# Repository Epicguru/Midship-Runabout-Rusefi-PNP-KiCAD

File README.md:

### Original Repo:
https://github.com/threepotMR2/Midship-Runabout-Rusefi-PNP-pcb

## MRR Epicguru Fork
This is a WIP KiCAD version of @threepotMR2 's Midship Runabout Rusefi project, which aims to be an affordable Plug & Play programmable ECU for the 1ZZFE or 2ZZ MR2 Spyder.  

**[Download the latest production files here (Gerbers, BOM, CPL)](https://github.com/Epicguru/Midship-Runabout-Rusefi-PNP-KiCAD/releases/latest)**  
I do not recommend ordering this version of the board yet, it is untested.

Compared to the original, this has been done in [KiCAD 10](https://www.kicad.org/), which is free open source schematic and PCB design software. If you also use the [JLCPCB Tools plugin](https://github.com/bouni/kicad-jlcpcb-tools) then you will get all parts ready to send for manufacturing with JLCPCB in one click (though pay attention to the rotation of components! I have not yet done the rotation corrections in the project, so you will need to do it when you upload the production files!).  

<p align="center">

  <br>

</p>

## Changes compared to original

### Important
- It is now a 4-layer board with signal on the front and back and two inner ground layers. This should improve signal integrity and reduce noise, especially under the VR circuits and the new 3.3v buck converter. This only adds around 1.5 EUR per board.
- Added TVS protection diodes  to the high and low-side relay switches. I haven't been able to verify whether the car's relays have built-in diodes (if they do they don't show up on wiring diagrams), but if they don't then each time they are switched then the coils will shove huge voltage spikes through the PhotoMOS which will kill them over time. If they do have built-in diodes, adding these extra ones doesn't hurt.
- Changed PhotoMOS fuses: the original fuses were 1A fast-blow fuses. The PhotoMOS are rated for 0.55A continuous. I have replaced the fuses with 0.5A hold, 1A trip resettable PTCs. It means that they still protect against short-circuits, but don't need replacing in that event.
- Replaced various resistors that were out-of-spec:
  - **R24**: This resistor was a 330 Ohm 0603 part that was limiting current to the PhotoMOS. The resistance was fine, allowing around 40mA through the LED vs 50mA max spec, but at that current it was dissipating around 0.5W of heat which is well above the 0.1W it is rated for. The resistor would cook over time, especially in a sealed case. It failing would turn the main relay off which could range from very annoying to really dangerous.
  - **R22**: This is the BEAN pull-up resistor. Resistance is fine but again it burns too much power: 0.2W in a 0.1W spec part. Changed to a larger package rated for 0.5W, same resistance.
  - **R15**: Tach output resistor. Did not really need changing but it was swapped for a higher power anti-surge resistor that just means that if you accidentally short the tach output (such as touching tach to chassis when removing dash) it won't burn the resistor out.
- Changed 12V input surge clamp to 18V, 600W part to protect U10 (buck converter) and U14 (tach output opto). The original 15V standoff was a little too close to normal charging voltage for my liking, increasing to 18 won't hurt anything on the circuit. I still need to improve this protection, but it should be fine for now.

### Other fixes & changes
- Fixed A/C pressure switch hardware: the manual says that you will get between 9V and 14V when pressure is good, and '-' when the pressure is bad. I haven't been able to figure out if that means LOW or just floating, but it's a problem either way.   
The problem with the original circuitry is that it relied on the voltage difference between the switch and VIN. If VIN happens to be too close to the P/S voltage, then the LED will not turn on. That leaves GPIO21 floating. Because there is no pull-up/down enabled in the firmware, I suspect that it was simply drifting HIGH which is why it was still working.  
More concerning is that if there is a fault: if the switch goes LOW then all of VIN is going to go through the LED, which puts R13 out-of-spec (~0.2W rated at 0.1W), and it will also still read as 'OK' on the ESP32. If the switch goes floating then we are back to the floating GPIO21 scenario, where it will probably still drift high.
  - I've fixed this by shuffling things around so that the A/C switch is now the LED driver. If it goes LOW or floating, then the LED turns off. If the LED turns off then there is an additional pull-down resistor on the output to make sure that it is low without having to rely on firmware pull-down.  
    
- Swapped 3.3v LDO for an automotive-grade buck converter. The LDO is fine for tiny currents but as current increases it starts to burn lots of power.
  - On the original board it was around 1.4W of heat produced, including the optocouplers. If you want to connect to the ESP32 Wifi then it could increase up to around 1.7W, which will get very toasty in an enclosed case. On the original board there is also a mistake that makes this worse, the large tab is not connected to the ground plane. The large tab is supposed to act as a heat sink by putting heat into the copper. It is not connected and so it will get even hotter. The LM2937 has a thermal-shutdown of 150C which isn't hard to reach without a heatsink and that much current. It's probably fine with the ESP32 WiFi turned off and a heat sink on it.  

  - The buck converter is a lot more efficient and costs almost exactly the same. The only disadvantage is that it can't handle huge input voltage spikes, see notes above.
- Populated all spare connections on the 'magic 5th connector'. There are now:
  - 4 analogue inputs (one has a 500k pull-down).
  - 1 digital input with a 10k pull-up.
- Added 1-pin male headers to the missing slots on the board.
- All male headers are now gold-plated and rated for 3A each. This should allow using female headers soldered on to the uaEFI to allow you to swap between daughter-boards without desoldering the RUS. Needs testing, might be too tall for the stock ECU case.
- Almost all power traces have been beefed up, especially the 12V input. 12V in can carry up to 4A if you are using the onboard wideband controller, so I've erred on the side of caution.
- Improved clearance around the crank and cam VR traces and do not route them through vias: these are very high voltage and noisy, so they have been kept on the top layer and away from other inputs as much as possible.

### Minor changes
- Added a jumper for the CAN bus termination resistor. If you have an external dash or logging device that has one soldered in, you can just remove the jumper rather than having to de-solder it.
- Added a mirrored set of female headers for the ESP32. That just makes probing easier, and lets you quite easily bodge in new circuitry. It may make it so that you have to use a 90-degree USB connector on the RUS since there is less space now.
- Added missing second ESP32 GND connection
- Added several test-points.

## Doubts
- The original board the stock OX1A pin was tied to signal ground. I'm not sure if that is a mistake or if Threepot was using the stock sensor plug for something else. I've added a jumper to either keep it tied to signal ground or just leave it floating. If the user wants to keep the stock sensor plugged in, for some reason, then the jumper should not be used.
- The original schematic and gerber/BOM files are slightly out-of-sync and the most significant change seems to be the VR conditioning capacitors. I haven't spent enough time researching these VR chips to know what the correct values are, so I've trusted what the JLCPCB BOM part number says and used those capacitor values.

## Does it work?
No clue, I've ordered one to try.  
I'll update the repo once I have had a chance to test it.

## Can it run the stock car?
No, you need an external wideband sensor in the exhaust, and the stock narrowband sensors need to be removed or they will be destroyed.

## How much does it cost?
You have to source the connector which can be had for around 25$ straight from the supplier, or 45$ from the RusEFI ebay shop.  
You also need the 17 pin 5th connector which is just a few dollars from China.
The board itself, with the components specified, costs around 70-100$ from JLCPCB. If you order many of them, the cost will be closer to 60$ per assembled board. If you order just two (minimum amount), expect around 100$ per board.  
The RusEFI uaEFI is around 150$.  

Overall, including the rusEFI & connectors, shipping, import duties and taxes, it cost me around 250 EUR per ECU when building two of them.

## Future plans/work
- [ ] Improve power input protections, including constant reverse polarity protection.
- [ ] Add ESD protection to 5th connector pins.
- [ ] Add ADC chip(s) and screw terminals. Using LUA scripting, you can effectively get 2 more 'free' analogue inputs to the ECU which can be used for anything, and you can get up to 6 additional analogue inputs that can be used for just logging.  
But, you can also use any number of inputs to be applied directly to the tune, or used to replace un-populated physical pins. That can be used to do two interesting things:
   - Create custom buttons/switches that do things like toggle launch control, boost control etc. without having to use any of the ECU's limited physical/virtual inputs.
   - Effectively allows you to 're-wire' unused physical pins without having to actually solder anything on the RUS.

## Are these available/for sale?
Keeping with the spirit of @threepotMR2 's MRR project, this version is open source. You can download all the files needed to have this manufactured, and you can buy a rusEFI uaEFI. If you know how to solder and have ~300$ to burn, you can get everything you need.  

I would like to eventually sell a complete assembled kit, including a 3D printed case, MAP air input, USB port etc. completely ready for use without having to touch the original ECU. I also have a gauge pod project, intended for MR2 turbo cars, that works with this ECU, which I would like to publish and maybe sell.  

ThreepotMR2 plans on selling his design as a kit, so that will be the place to buy one especially if you live in the UK. Since this is 99% his design, work and months testing I will not be selling these directly in the foreseeable future.  

In the future, if he isn't bothered by it, I might still turn these into a product that I sell directly which I'm sure people in Europe would appreciate: shipping and import duty costs are half of the price for most of these components and boards, so extra inter-continental fees really hurt.

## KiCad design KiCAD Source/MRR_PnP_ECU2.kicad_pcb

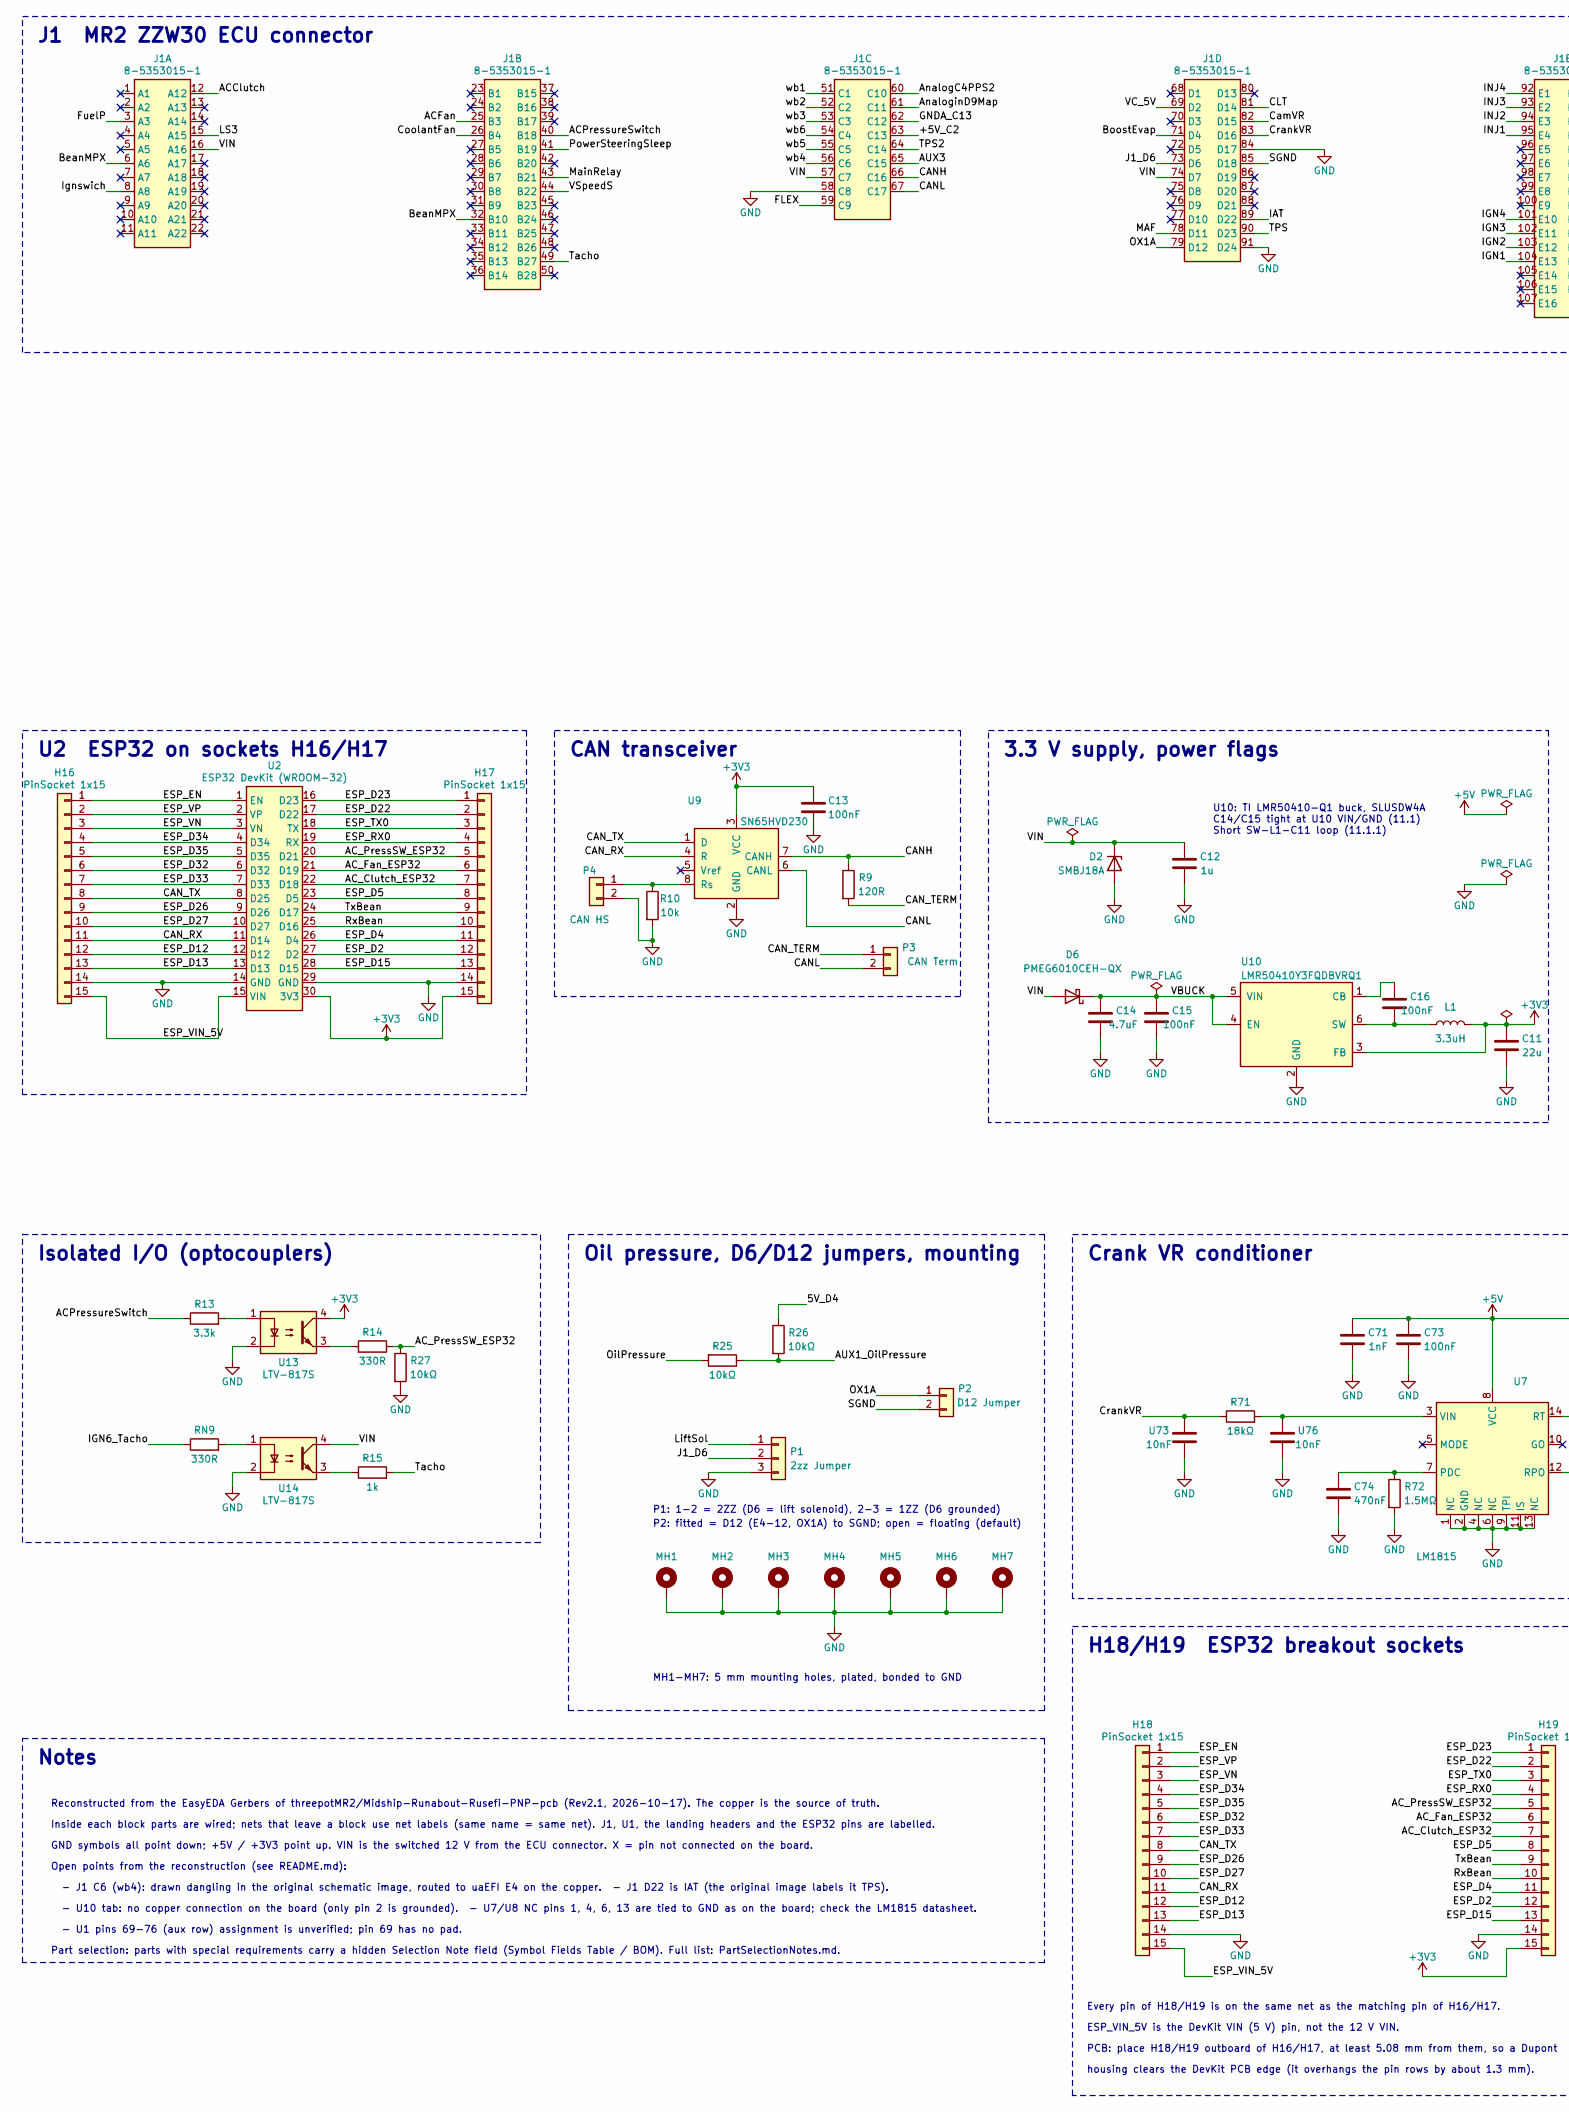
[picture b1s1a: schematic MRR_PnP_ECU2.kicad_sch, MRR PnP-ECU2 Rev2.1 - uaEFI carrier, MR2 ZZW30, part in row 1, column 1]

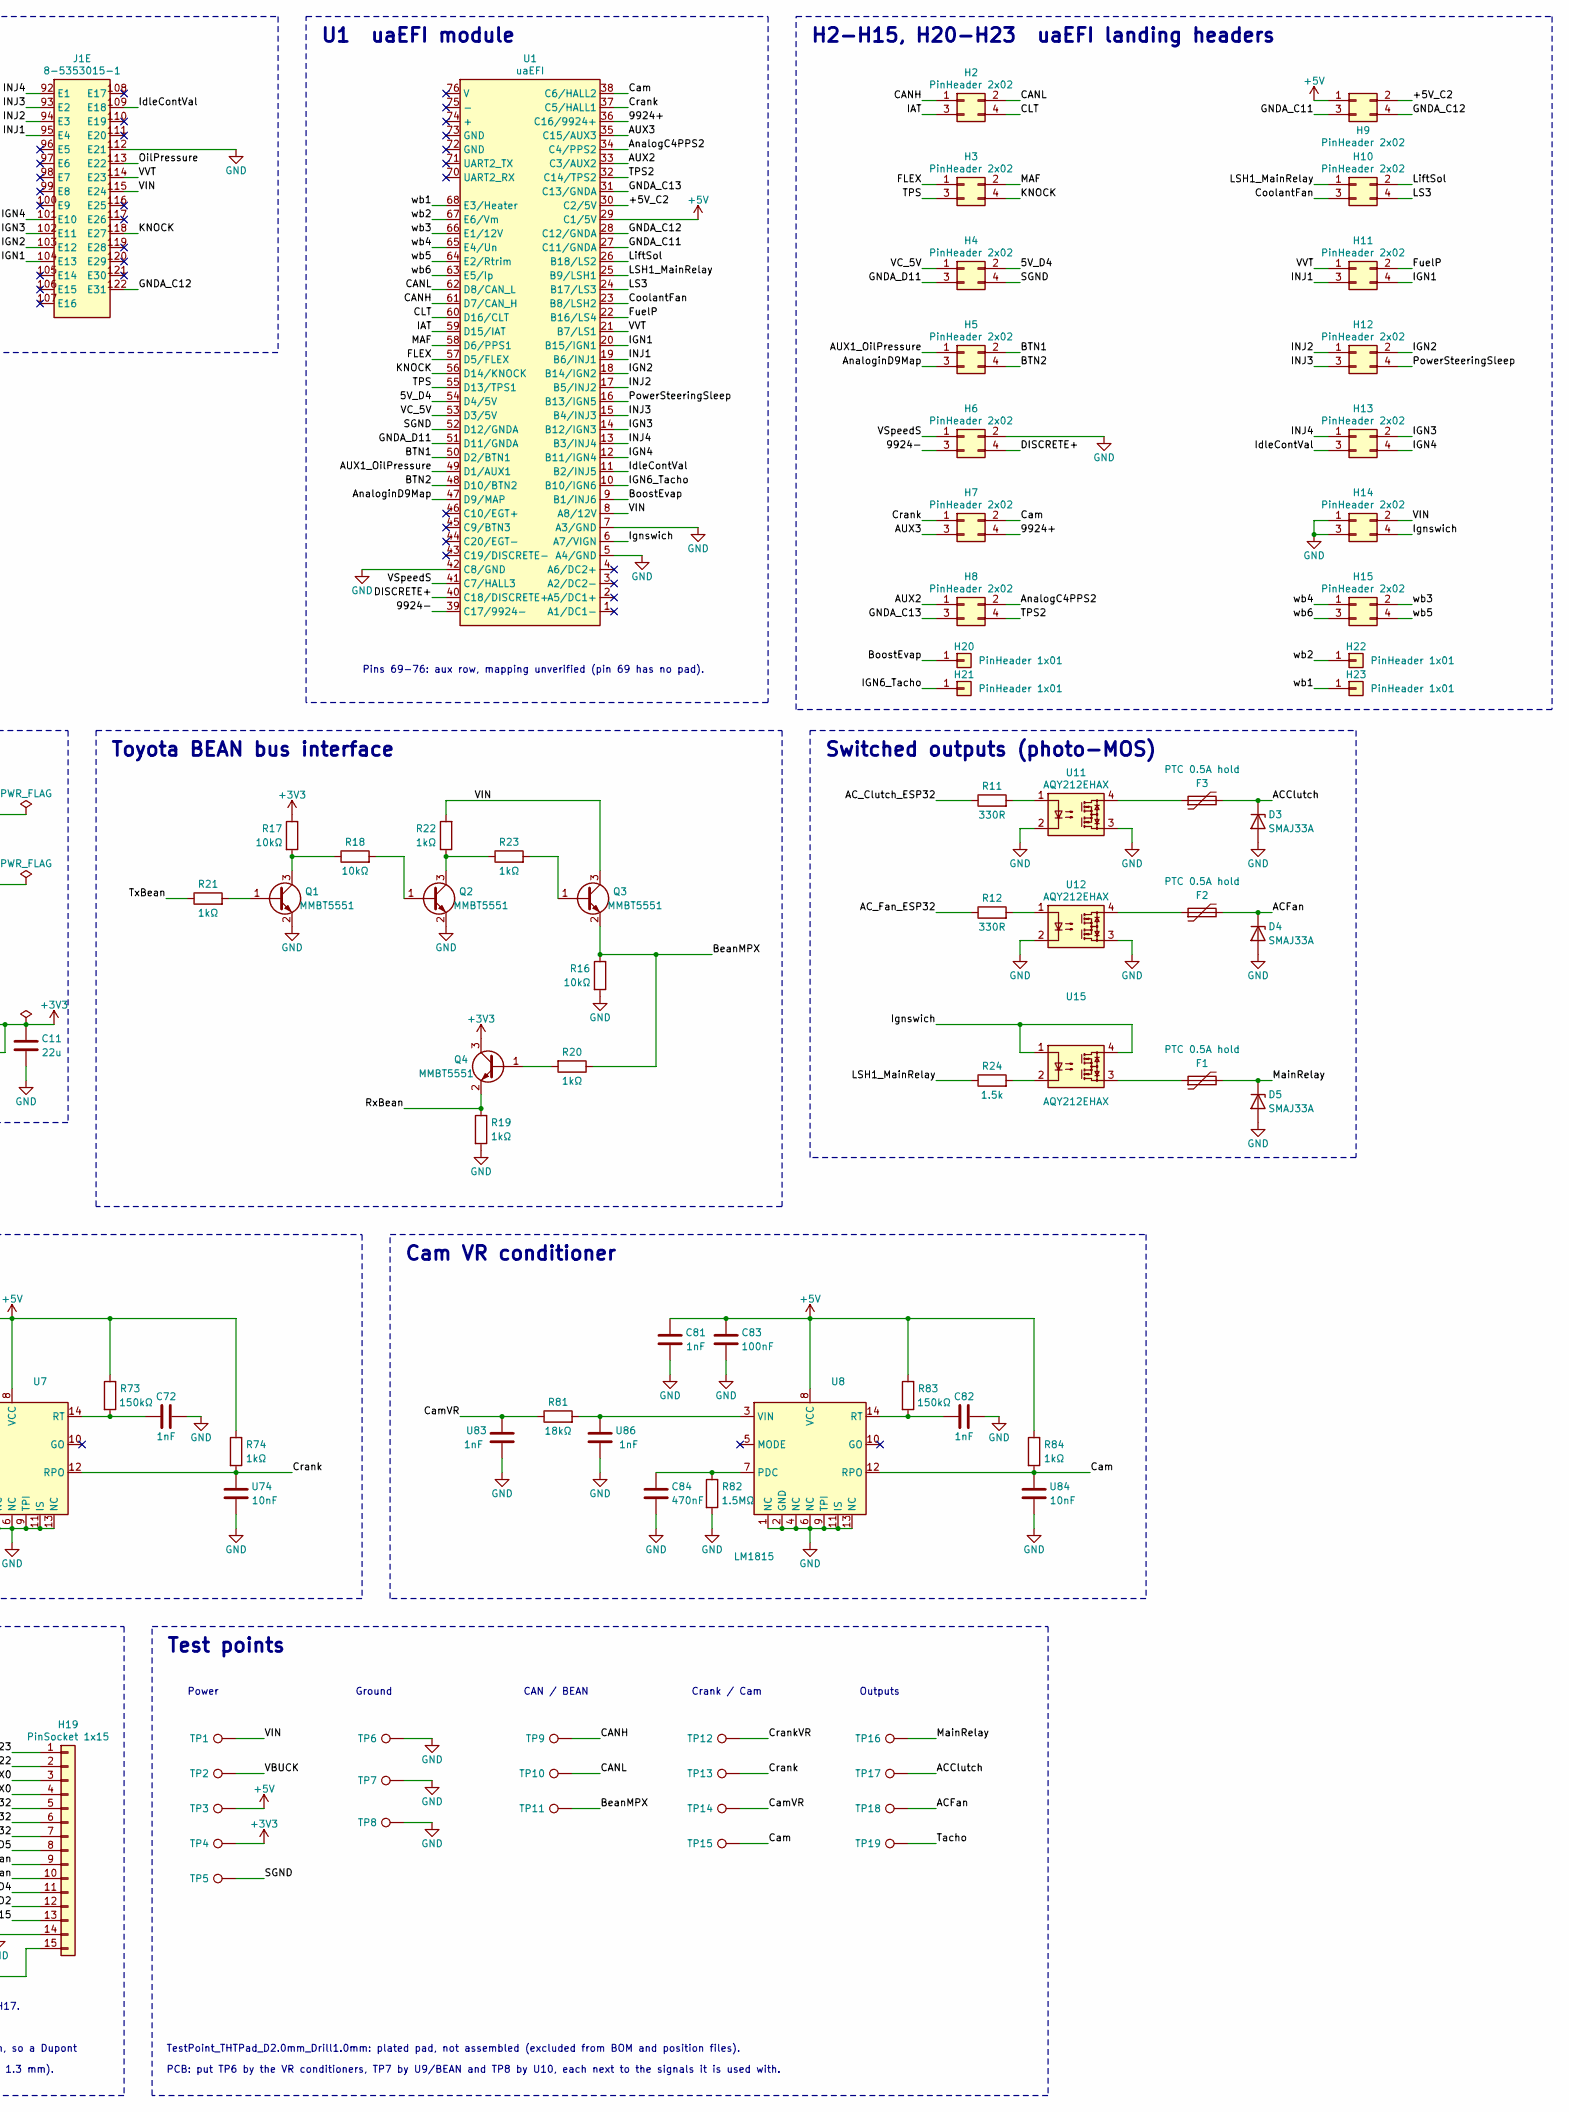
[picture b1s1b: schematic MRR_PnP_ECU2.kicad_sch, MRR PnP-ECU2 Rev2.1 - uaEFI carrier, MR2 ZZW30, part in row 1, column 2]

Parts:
C11: 22u; C_1206_3216Metric; MPN CL31A226KAHNNNE; LCSC C12891
C12: 1u; C_0603_1608Metric; MPN CL10B105KB8NQNC; LCSC C5199872
C13, C15, C16, C73, C83: 100nF; C_0603_1608Metric; MPN CC0603KRX7R9BB104; LCSC C14663
C14: 4.7uF; C_0805_2012Metric; MPN GRM21BZ71H475KE15L; LCSC C437557
C71, C81: 1nF; C_0603_1608Metric; MPN CL10B102KB8NNNC; LCSC C1588
C72, C82: 1nF; C_0603_1608Metric; MPN GCM1885C2A102JA16D; LCSC C437457
C74, C84: 470nF; C_0603_1608Metric; MPN CL10B474KA8NNNC; LCSC C1623
D2: SMBJ18A; D_SMB; MPN SMBJ18AQ; LCSC C5861908
D3, D4, D5: SMAJ33A; D_SMA; MPN SMAJ33A; LCSC C41376399
D6: PMEG6010CEH-QX; D_SOD-123F; MPN PMEG6010CEH-QX; LCSC C5311567
F1, F2, F3: PTC 0.5A hold; Fuse_1206_3216Metric; MPN JK-nSMD050-30; LCSC C720075
H2, H3, H4, H5, H6, H7, H8, H9, H10, H11, H12, H13, H14, H15: PinHeader 2x02; PinHeader_2x02_P2.54mm_uaEFI; MPN 2.54-2*2PPin; LCSC C66690
H16, H17, H18, H19: PinSocket 1x15; PinSocket_1x15_P2.54mm_Vertical; MPN B-2200S15P-A120; LCSC C124408
H20, H21, H22, H23: PinHeader 1x01; PinHeader_1x01_P2.54mm_uaEFI; MPN 2.54-1*1PPin; LCSC C81276
J1: 8-5353015-1; Toyota_ZZW30_ECU_122pin_MRR
L1: 3.3uH; L_Sunlord_SWPA4030S; MPN SWPA4030S3R3MT; LCSC C15269
MH1, MH2, MH3, MH4, MH5, MH6, MH7: MountingHole 5mm; MountingHole_5mm_Pad_7mm
P1: 2zz Jumper; PinHeader_1x03_P2.54mm_Vertical; MPN PZ254V-11-03P; LCSC C2937625
P2: D12 Jumper; PinHeader_1x02_P2.54mm_Vertical; MPN PZ254V-11-02P; LCSC C492401
P3: CAN Term; PinHeader_1x02_P2.54mm_Vertical; MPN PZ254V-11-02P; LCSC C492401
P4: CAN HS; PinHeader_1x02_P2.54mm_Vertical; MPN PZ254V-11-02P; LCSC C492401
Q1, Q2, Q3, Q4: MMBT5551; SOT-23; MPN MMBT5551(RANGE:200-300); LCSC C2145
R9: 120R; R_0603_1608Metric; MPN 0603WAF1200T5E; LCSC C22787
R10: 10k; R_0603_1608Metric; MPN 0603WAF1002T5E; LCSC C25804
R11, R12, R14: 330R; R_0603_1608Metric; MPN 0603WAF3300T5E; LCSC C23138
R13: 3.3k; R_0603_1608Metric; MPN 0603WAF3301T5E; LCSC C22978
R15: 1k; R_0603_1608Metric; MPN ESR03EZPF1001; LCSC C2653986
R16, R17, R18, R25, R26, R27: 10kΩ; R_0603_1608Metric; MPN 0603WAF1002T5E; LCSC C25804
R19, R20, R21, R23, R74, R84: 1kΩ; R_0603_1608Metric; MPN 0603WAF1001T5E; LCSC C21190
R22: 1kΩ; R_1210_3225Metric; MPN 1210W2F1001T5E; LCSC C52444
R24: 1.5k; R_1206_3216Metric; MPN 1206W4F1501T5E; LCSC C26030
R71, R81: 18kΩ; R_1210_3225Metric; MPN 1210W2F1802T5E; LCSC C67557
R72, R82: 1.5MΩ; R_0603_1608Metric; MPN 0603WAF1504T5E; LCSC C4172
R73, R83: 150kΩ; R_0603_1608Metric; MPN 0603WAF1503T5E; LCSC C22807
RN9: 330R; R_0603_1608Metric; MPN 0603WAF3300T5E; LCSC C23138
TP1: VIN; TestPoint_THTPad_D2.0mm_Drill1.0mm
TP2: VBUCK; TestPoint_THTPad_D2.0mm_Drill1.0mm
TP3: +5V; TestPoint_THTPad_D2.0mm_Drill1.0mm
TP4: +3V3; TestPoint_THTPad_D2.0mm_Drill1.0mm
TP5: SGND; TestPoint_THTPad_D2.0mm_Drill1.0mm
TP6, TP7, TP8: GND; TestPoint_THTPad_D2.0mm_Drill1.0mm
TP9: CANH; TestPoint_THTPad_D2.0mm_Drill1.0mm
TP10: CANL; TestPoint_THTPad_D2.0mm_Drill1.0mm
TP11: BeanMPX; TestPoint_THTPad_D2.0mm_Drill1.0mm
TP12: CrankVR; TestPoint_THTPad_D2.0mm_Drill1.0mm
TP13: Crank; TestPoint_THTPad_D2.0mm_Drill1.0mm
TP14: CamVR; TestPoint_THTPad_D2.0mm_Drill1.0mm
TP15: Cam; TestPoint_THTPad_D2.0mm_Drill1.0mm
TP16: MainRelay; TestPoint_THTPad_D2.0mm_Drill1.0mm
TP17: ACClutch; TestPoint_THTPad_D2.0mm_Drill1.0mm
TP18: ACFan; TestPoint_THTPad_D2.0mm_Drill1.0mm
TP19: Tacho; TestPoint_THTPad_D2.0mm_Drill1.0mm
U1: uaEFI; uaEFI_Carrier_MRR
U2: ESP32 DevKit (WROOM-32); ESP32_DevKit_30pin_MRR; MPN ESP32 WROOM-32 ESP32-S
U7, U8: LM1815; SOIC-14_3.9x8.7mm_P1.27mm; MPN LM1815MX/NOPB; LCSC C2878578
U9: SN65HVD230; SOIC-8_3.9x4.9mm_P1.27mm; MPN SN65HVD230DR; LCSC C12084
U10: LMR50410Y3FQDBVRQ1; SOT-23-6; MPN LMR50410Y3FQDBVRQ1; LCSC C5219374
U11, U12, U15: AQY212EHAX; SMDIP-4_W9.53mm; MPN AQY212EHAX; LCSC C29276
U13, U14: LTV-817S; SMDIP-4_W9.53mm; MPN LTV-817S-TA1-C; LCSC C109227
U73: 10nF; C_0603_1608Metric; MPN CC0603KRX7R0BB103; LCSC C107059
U74, U76, U84: 10nF; C_0603_1608Metric; MPN 0603B103K500NT; LCSC C57112
U83, U86: 1nF; C_0603_1608Metric; MPN GCM1885C2A102JA16D; LCSC C437457

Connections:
+3V3: C11.2, C13.1, H17.15, H19.15, L1.2, Q4.3 (C), R17.1, TP4.1 (1_1), U2.30 (3V3), U9.3 (VCC), U10.3 (FB), U13.4
+5V: C71.1, C73.1, C81.1, C83.1, H9.1, R73.1, R74.1, R83.1, R84.1, TP3.1 (1_1), U1.29 (C1/5V), U7.8 (VCC), U8.8 (VCC)
/5V_D4: H4.2, R26.1, U1.54 (D4/5V)
/9924+: H7.4, U1.36 (C16/9924+)
/9924-: H6.3, U1.39 (C17/9924-)
/+5V_C2: H9.2, J1.63 (C13), U1.30 (C2/5V)
/ACClutch: D3.1 (K), F3.2, J1.12 (A12), TP17.1 (1_1)
/ACFan: D4.1 (K), F2.2, J1.25 (B3), TP18.1 (1_1)
/ACPressureSwitch: J1.40 (B18), R13.1
/AC_Clutch_ESP32: H17.7, H19.7, R11.1, U2.22 (D18)
/AC_Fan_ESP32: H17.6, H19.6, R12.1, U2.21 (D19)
/AC_PressSW_ESP32: H17.5, H19.5, R14.1, R27.1, U2.20 (D21)
/AUX1_OilPressure: H5.1, R25.1, R26.2, U1.49 (D1/AUX1)
/AUX2: H8.1, U1.33 (C3/AUX2)
/AUX3: H7.3, J1.65 (C15), U1.35 (C15/AUX3)
/AnalogC4PPS2: H8.2, J1.60 (C10), U1.34 (C4/PPS2)
/AnaloginD9Map: H5.3, J1.61 (C11), U1.47 (D9/MAP)
/BTN1: H5.2, U1.50 (D2/BTN1)
/BTN2: H5.4, U1.48 (D10/BTN2)
/BeanMPX: J1.6 (A6), J1.32 (B10), Q3.2 (E), R16.1, R20.1, TP11.1 (1_1)
/BoostEvap: H20.1, J1.71 (D4), U1.9 (B1/INJ6)
/CANH: H2.1, J1.66 (C16), R9.1, TP9.1 (1_1), U1.61 (D7/CAN_H), U9.7 (CANH)
/CANL: H2.2, J1.67 (C17), P3.2, TP10.1 (1_1), U1.62 (D8/CAN_L), U9.6 (CANL)
/CAN_RX: H16.11, H18.11, U2.11 (D14), U9.4 (R)
/CAN_TERM: P3.1, R9.2
/CAN_TX: H16.8, H18.8, U2.8 (D25), U9.1 (D)
/CLT: H2.4, J1.81 (D14), U1.60 (D16/CLT)
/Cam: H7.2, R84.2, TP15.1 (1_1), U1.38 (C6/HALL2), U8.12 (RPO), U84.1
/CamVR: J1.82 (D15), R81.1, TP14.1 (1_1), U83.1
/CoolantFan: H10.3, J1.26 (B4), U1.23 (B8/LSH2)
/Crank: H7.1, R74.2, TP13.1 (1_1), U1.37 (C5/HALL1), U7.12 (RPO), U74.1
/CrankVR: J1.83 (D16), R71.1, TP12.1 (1_1), U73.1
/DISCRETE+: H6.4, U1.40 (C18/DISCRETE+)
/ESP_D2: H17.12, H19.12, U2.27 (D2)
/ESP_D4: H17.11, H19.11, U2.26 (D4)
/ESP_D5: H17.8, H19.8, U2.23 (D5)
/ESP_D12: H16.12, H18.12, U2.12 (D12)
/ESP_D13: H16.13, H18.13, U2.13 (D13)
/ESP_D15: H17.13, H19.13, U2.28 (D15)
/ESP_D22: H17.2, H19.2, U2.17 (D22)
/ESP_D23: H17.1, H19.1, U2.16 (D23)
/ESP_D26: H16.9, H18.9, U2.9 (D26)
/ESP_D27: H16.10, H18.10, U2.10 (D27)
/ESP_D32: H16.6, H18.6, U2.6 (D32)
/ESP_D33: H16.7, H18.7, U2.7 (D33)
/ESP_D34: H16.4, H18.4, U2.4 (D34)
/ESP_D35: H16.5, H18.5, U2.5 (D35)
/ESP_EN: H16.1, H18.1, U2.1 (EN)
/ESP_RX0: H17.4, H19.4, U2.19 (RX)
/ESP_TX0: H17.3, H19.3, U2.18 (TX)
/ESP_VIN_5V: H16.15, H18.15, U2.15 (VIN)
/ESP_VN: H16.3, H18.3, U2.3 (VN)
/ESP_VP: H16.2, H18.2, U2.2 (VP)
/FLEX: H3.1, J1.59 (C9), U1.57 (D5/FLEX)
/FuelP: H11.2, J1.3 (A3), U1.22 (B16/LS4)
/GNDA_C11: H9.3, U1.27 (C11/GNDA)
/GNDA_C12: H9.4, J1.122 (E31), U1.28 (C12/GNDA)
/GNDA_C13: H8.3, J1.62 (C12), U1.31 (C13/GNDA)
/GNDA_D11: H4.3, U1.51 (D11/GNDA)
/IAT: H2.3, J1.89 (D22), U1.59 (D15/IAT)
/IGN1: H11.4, J1.104 (E13), U1.20 (B15/IGN1)
/IGN2: H12.2, J1.103 (E12), U1.18 (B14/IGN2)
/IGN3: H13.2, J1.102 (E11), U1.14 (B12/IGN3)
/IGN4: H13.4, J1.101 (E10), U1.12 (B11/IGN4)
/IGN6_Tacho: H21.1, RN9.1, U1.10 (B10/IGN6)
/INJ1: H11.3, J1.95 (E4), U1.19 (B6/INJ1)
/INJ2: H12.1, J1.94 (E3), U1.17 (B5/INJ2)
/INJ3: H12.3, J1.93 (E2), U1.15 (B4/INJ3)
/INJ4: H13.1, J1.92 (E1), U1.13 (B3/INJ4)
/IdleContVal: H13.3, J1.109 (E18), U1.11 (B2/INJ5)
/Ignswich: H14.4, J1.8 (A8), U1.6 (A7/VIGN), U15.1, U15.4
/J1_D6: J1.73 (D6), P1.2
/KNOCK: H3.4, J1.118 (E27), U1.56 (D14/KNOCK)
/LS3: H10.4, J1.15 (A15), U1.24 (B17/LS3)
/LSH1_MainRelay: H10.1, R24.1, U1.25 (B9/LSH1)
/LiftSol: H10.2, P1.1, U1.26 (B18/LS2)
/MAF: H3.2, J1.78 (D11), U1.58 (D6/PPS1)
/MainRelay: D5.1 (K), F1.2, J1.43 (B21), TP16.1 (1_1)
/OX1A: J1.79 (D12), P2.1
/OilPressure: J1.113 (E22), R25.2
/PowerSteeringSleep: H12.4, J1.41 (B19), U1.16 (B13/IGN5)
/RxBean: H17.10, H19.10, Q4.2 (E), R19.1, U2.25 (D16)
/SGND: H4.4, J1.85 (D18), P2.2, TP5.1 (1_1), U1.52 (D12/GNDA)
/TPS: H3.3, J1.90 (D23), U1.55 (D13/TPS1)
/TPS2: H8.4, J1.64 (C14), U1.32 (C14/TPS2)
/Tacho: J1.49 (B27), R15.2, TP19.1 (1_1)
/TxBean: H17.9, H19.9, R21.1, U2.24 (D17)
/VBUCK: C14.2, C15.2, D6.1 (K), TP2.1 (1_1), U10.4 (EN), U10.5 (VIN)
/VC_5V: H4.1, J1.69 (D2), U1.53 (D3/5V)
/VIN: C12.2, D2.1 (K), D6.2 (A), H14.2, J1.16 (A16), J1.57 (C7), J1.74 (D7), J1.115 (E24), Q3.3 (C), R22.2, TP1.1 (1_1), U1.8 (A8/12V), U14.4
/VSpeedS: H6.1, J1.44 (B22), U1.41 (C7/HALL3)
/VVT: H11.1, J1.114 (E23), U1.21 (B7/LS1)
/wb1: H23.1, J1.51 (C1), U1.68 (E3/Heater)
/wb2: H22.1, J1.52 (C2), U1.67 (E6/Vm)
/wb3: H15.2, J1.53 (C3), U1.66 (E1/12V)
/wb4: H15.1, J1.56 (C6), U1.65 (E4/Un)
/wb5: H15.4, J1.55 (C5), U1.64 (E2/Rtrim)
/wb6: H15.3, J1.54 (C4), U1.63 (E5/Ip)
GND: C11.1, C12.1, C13.2, C14.1, C15.1, C71.2, C72.2, C73.2, C74.1, C81.2, C82.2, C83.2, C84.1, D2.2 (A), D3.2 (A), D4.2 (A), D5.2 (A), H6.2, H14.1, H14.3, H16.14, H17.14, H18.14, H19.14, J1.58 (C8), J1.84 (D17), J1.91 (D24), J1.112 (E21), MH1.1 (1_1), MH2.1 (1_1), MH3.1 (1_1), MH4.1 (1_1), MH5.1 (1_1), MH6.1 (1_1), MH7.1 (1_1), P1.3, P4.2, Q1.2 (E), Q2.2 (E), R10.2, R16.2, R19.2, R27.2, R72.2, R82.2, TP6.1 (1_1), TP7.1 (1_1), TP8.1 (1_1), U1.5 (A4/GND), U1.7 (A3/GND), U1.42 (C8/GND), U2.14 (GND), U2.29 (GND), U7.1 (NC), U7.2 (GND), U7.4 (NC), U7.6 (NC), U7.9 (TPI), U7.11 (IS), U7.13 (NC), U8.1 (NC), U8.2 (GND), U8.4 (NC), U8.6 (NC), U8.9 (TPI), U8.11 (IS), U8.13 (NC), U9.2 (GND), U10.2 (GND), U11.2, U11.3, U12.2, U12.3, U13.2, U14.2, U73.2, U74.2, U76.2, U83.2, U84.2, U86.2
unnamed: F1.1, U15.3
unnamed: F2.1, U12.4
unnamed: F3.1, U11.4
unnamed: P4.1, R10.1, U9.8 (Rs)
unnamed: Q1.1 (B), R21.2
unnamed: Q1.3 (C), R17.2, R18.1
unnamed: Q2.1 (B), R18.2
unnamed: Q2.3 (C), R22.1, R23.1
unnamed: Q3.1 (B), R23.2
unnamed: Q4.1 (B), R20.2
unnamed: R11.2, U11.1
unnamed: R12.2, U12.1
unnamed: R13.2, U13.1
unnamed: R14.2, U13.3
unnamed: R15.1, U14.3
unnamed: R24.2, U15.2
unnamed: RN9.2, U14.1
unnamed: C74.2, R72.1, U7.7 (PDC)
unnamed: C72.1, R73.2, U7.14 (RT)
unnamed: R71.2, U7.3 (VIN), U76.1
unnamed: C84.2, R82.1, U8.7 (PDC)
unnamed: C82.1, R83.2, U8.14 (RT)
unnamed: R81.2, U8.3 (VIN), U86.1
unnamed: C16.2, U10.1 (CB)
unnamed: C16.1, L1.1, U10.6 (SW)

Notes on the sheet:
3.3 V supply, power flags
- J1 C6 (wb4): drawn dangling in the original schematic image, routed to uaEFI E4 on the copper. - J1 D22 is IAT (the original image labels it TPS).
Reconstructed from the EasyEDA Gerbers of threepotMR2/Midship-Runabout-Rusefi-PNP-pcb (Rev2.1, 2026-10-17). The copper is the source of truth.
P2: fitted = D12 (E4-12, OX1A) to SGND; open = floating (default)
housing clears the DevKit PCB edge (it overhangs the pin rows by about 1.3 mm).
Ground
TestPoint_THTPad_D2.0mm_Drill1.0mm: plated pad, not assembled (excluded from BOM and position files).
Crank / Cam
Toyota BEAN bus interface
Notes
- U1 pins 69-76 (aux row) assignment is unverified; pin 69 has no pad.
Isolated I/O (optocouplers)
Switched outputs (photo-MOS)
CAN / BEAN
Every pin of H18/H19 is on the same net as the matching pin of H16/H17.
U1 uaEFI module
MH1-MH7: 5 mm mounting holes, plated, bonded to GND
Cam VR conditioner
P1: 1-2 = 2ZZ (D6 = lift solenoid), 2-3 = 1ZZ (D6 grounded)
Open points from the reconstruction (see README.md):
PCB: put TP6 by the VR conditioners, TP7 by U9/BEAN and TP8 by U10, each next to the signals it is used with.
U10: TI LMR50410-Q1 buck, SLUSDW4A C14/C15 tight at U10 VIN/GND (11.1) Short SW-L1-C11 loop (11.1.1)
Test points
Power
Oil pressure, D6/D12 jumpers, mounting
Outputs
U2 ESP32 on sockets H16/H17
J1 MR2 ZZW30 ECU connector
CAN transceiver
Pins 69-76: aux row, mapping unverified (pin 69 has no pad).
Inside each block parts are wired; nets that leave a block use net labels (same name = same net). J1, U1, the landing headers and the ESP32 pins are labelled.
- U10 tab: no copper connection on the board (only pin 2 is grounded). - U7/U8 NC pins 1, 4, 6, 13 are tied to GND as on the board; check the LM1815 datasheet.
Part selection: parts with special requirements carry a hidden Selection Note field (Symbol Fields Table / BOM). Full list: PartSelectionNotes.md.
H18/H19 ESP32 breakout sockets
GND symbols all point down; +5V / +3V3 point up. VIN is the switched 12 V from the ECU connector. X = pin not connected on the board.
H2-H15, H20-H23 uaEFI landing headers
PCB: place H18/H19 outboard of H16/H17, at least 5.08 mm from them, so a Dupont
Crank VR conditioner
ESP_VIN_5V is the DevKit VIN (5 V) pin, not the 12 V VIN.

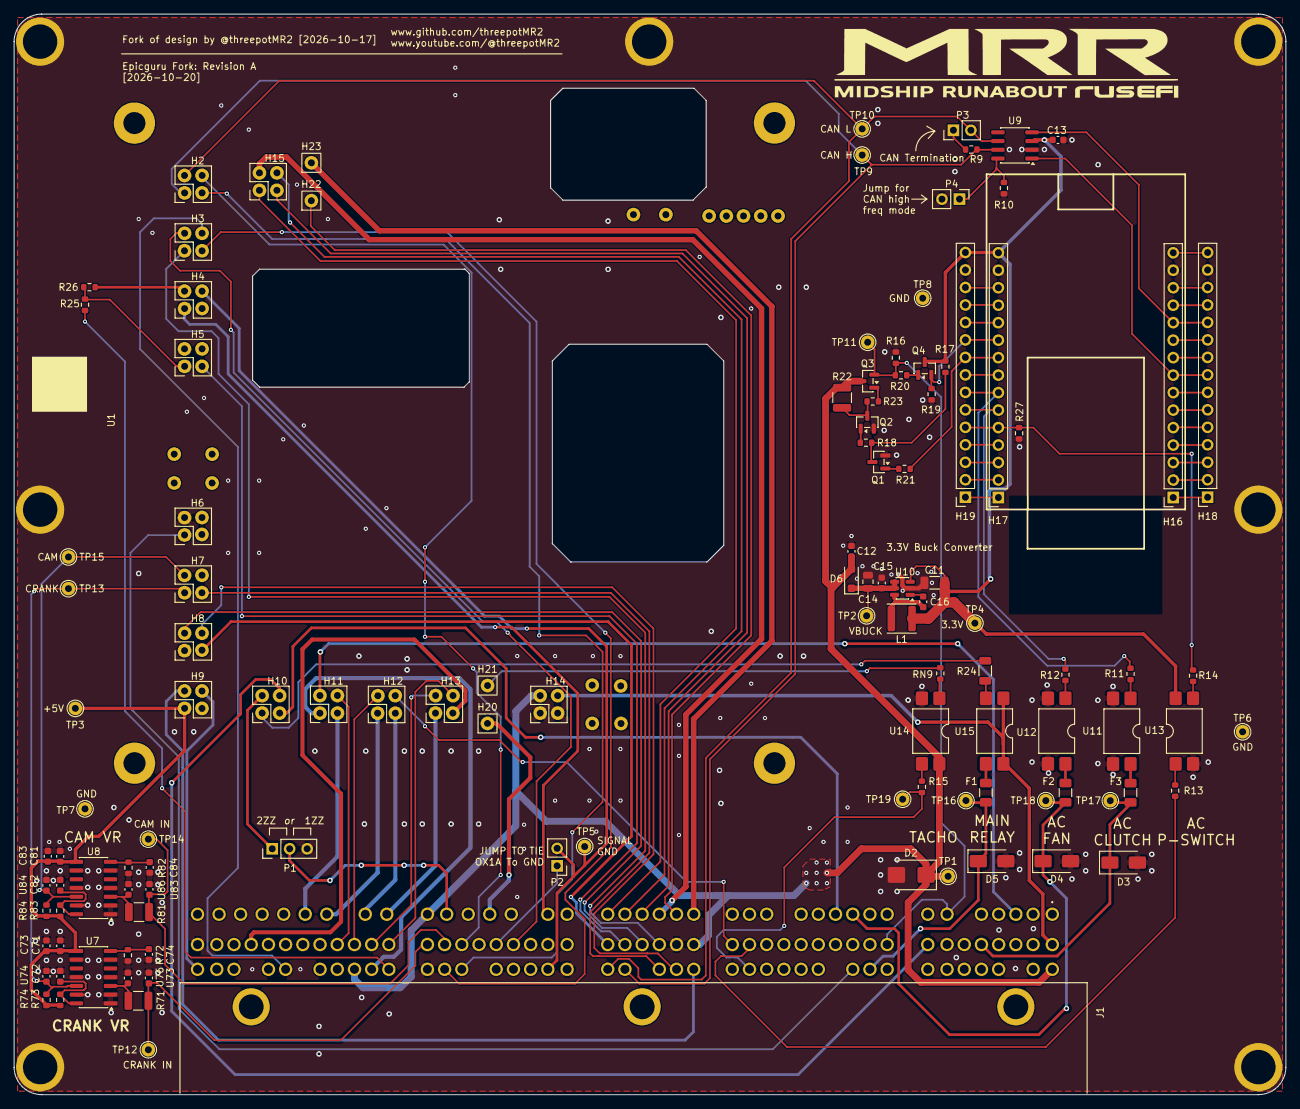
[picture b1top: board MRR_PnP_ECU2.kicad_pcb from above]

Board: 4 copper layers, 184.8 x 157.0 mm, 124 parts (0 on the bottom side), 124 nets.
